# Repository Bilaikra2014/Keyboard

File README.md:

# ⌨️ WirelessKeyboard Project

Ce projet a pour objectif la conception et la fabrication d'un clavier mécanique (Filaire USB-C / Sans-fil). Le système repose sur un écosystème ESP32 permettant une communication rapide et personnalisée. Ce projet est une première version de test, une autre version pourrait être conçue dans le but de rechercher encore plus de perfomance en utilisant des composants plus adaptés.

## 📋 Présentation du projet

Le projet consiste à créer deux dispositifs distincts :
1.  **Le Clavier (Émetteur) :** Gère la matrice de touches, la batterie et la communication.
2.  **Le Récepteur (Dongle) :** Reçoit les données sans fil et les transmet à l'ordinateur via USB.

L'architecture se divise en trois axes de développement :
* **Électronique :** Conception des schémas et des PCB.
* **Informatique :** Développement des firmwares d'émission et de réception.
* **Mécanique :** Conception CAO 3D du boîtier du clavier et de celui dongle.

---

## 🛠️ Spécifications Matérielles

### 1. Le Clavier (ESP32-S3)
Le choix de l'**ESP32-S3** est motivé par son support **USB natif**, indispensable pour le mode filaire.
* **Prise USB C** pour le mode filaire.
* **Alimentation :** Batterie LiPo 1S (3.7V).
* **Régulation :** Passage du 5V(USB)/3v7(Batterie) vers 3.3V via un régulateur de tension (LDO).
* **Gestion de charge :** Circuit de charge intégré permettant :
    * L'alimentation du µC via USB lors du branchement.
    * La recharge simultanée de la batterie.
    * Le basculement automatique sur batterie lors du débranchement.

### 2. Le Récepteur (ESP32-S3-MINI)

L'**ESP32-S3-MINI** est utilisé pour son format compact et son coût réduit. Il fait office de pont entre le clavier et le PC.
* **Prise USB A** pour le brancher à l'ordinateur.
* **Interface :** Prise USB-A mâle.
* **Alimentation :** LDO convertissant le 5V USB en 3.3V.
* **Contrôles physiques :**
    * **Bouton BOOT :** Maintien du GPIO 9 à la masse pour le mode téléchargement.
    * **Bouton RESET :** Redémarrage du contrôleur pour les phases de test.
* **Câblage USB natif :**
    * `D+` ↔ GPIO 19
    * `D-` ↔ GPIO 18
    * `V+` ↔ Entrée LDO
    * `GND` ↔ Masse commune

---

## 📂 Structure du projet

Chaque sous-structure du projet aura son propre fichier Readme dédiée à la partie qu'elle traite.

```text
.
├── 📁 Electronique        # Schémas et PCB (KiCad)
│   ├── 📁 Lib              # Librairie Kicad
│   ├── 📁 Clavier          # Code de l'émetteur
│   └── 📁 Recepteur        # Code du récepteur
├── 📁 Informatique        # Code source ESP32
│   ├── 📁 Clavier          # Code de l'émetteur
│   └── 📁 Recepteur        # Code du récepteur
├── 📁 Mecanique          # Modèles 3D (STL/STEP)
└── README.md                #README global du projet

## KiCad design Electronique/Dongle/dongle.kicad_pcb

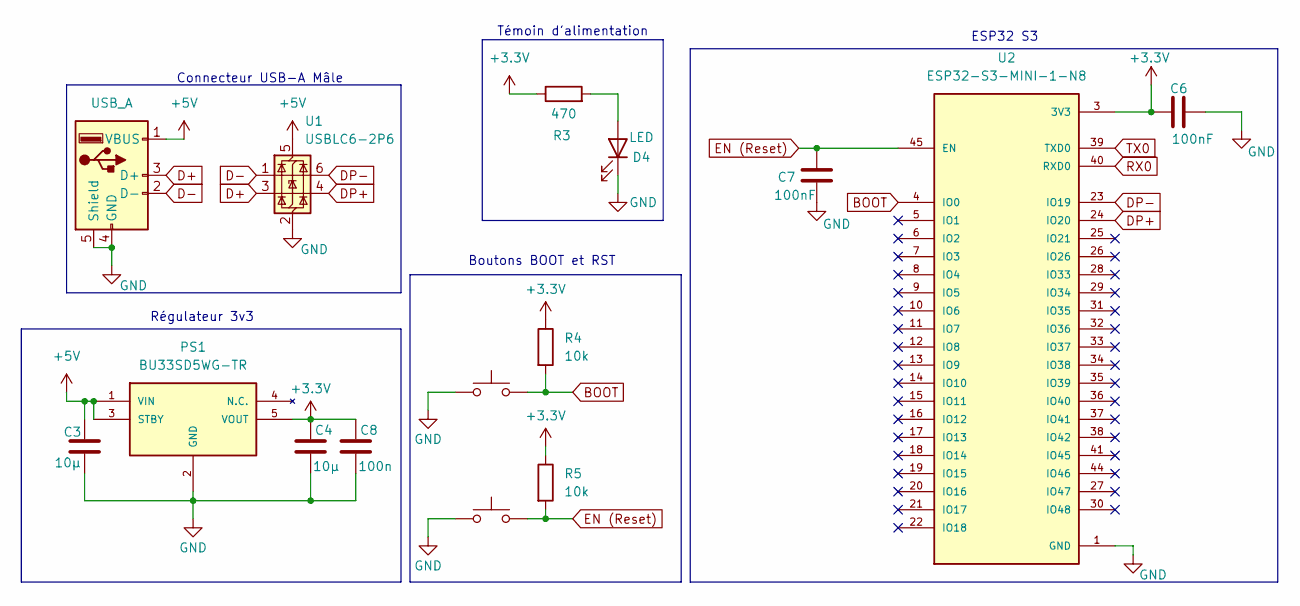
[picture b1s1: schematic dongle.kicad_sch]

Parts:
C3, C4: 10µ; C_0603_1608Metric_Pad1.08x0.95mm_HandSolder
C6, C7: 100nF; C_0603_1608Metric_Pad1.08x0.95mm_HandSolder
C8: 100n; C_0603_1608Metric_Pad1.08x0.95mm_HandSolder
D4: LED; LED_0603_1608Metric
J1: USB_A; USB_A_CNCTech_1001-011-01101_Horizontal
PS1: BU33SD5WG-TR; SOT95P280X125-5N; MOUSER_PART_NUMBER 755-BU33SD5WG-TR
R3: 470; R_0805_2012Metric
R4, R5: 10k; R_0805_2012Metric
SW3: BOOT; 434771025826
SW4: RST; 434771025826
U1: USBLC6-2P6; SOT-23-6
U2: ESP32-S3-MINI-1-N8; PARTREV v0.6

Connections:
+3.3V: C4.1, C6.2, C8.1, PS1.5 (VOUT), R3.1, R4.1, R5.1, U2.3 (3V3)
+5V: C3.1, J1.1 (VBUS), PS1.1 (VIN), PS1.3 (STBY), U1.5 (VBUS)
BOOT: R4.2, SW3.2, U2.4 (IO0)
D+: J1.3 (D+), U1.3 (I/O2)
D-: J1.2 (D-), U1.1 (I/O1)
DP+: U1.4 (I/O2), U2.24 (IO20)
DP-: U1.6 (I/O1), U2.23 (IO19)
EN (Reset): C7.1, R5.2, SW4.2, U2.45 (EN)
GND: C3.2, C4.2, C6.1, C7.2, C8.2, D4.1 (K), J1.4 (GND), J1.5 (Shield), PS1.2 (GND), SW3.1, SW4.1, U1.2 (GND), U2.1 (GND), U2.2 (GND), U2.42 (GND), U2.43 (GND), U2.46 (GND), U2.47 (GND), U2.48 (GND), U2.49 (GND), U2.50 (GND), U2.51 (GND), U2.52 (GND), U2.53 (GND), U2.54 (GND), U2.55 (GND), U2.56 (GND), U2.57 (GND), U2.58 (GND), U2.59 (GND), U2.60 (GND), U2.61 (GND), U2.61_1 (GND), U2.61_2 (GND), U2.61_3 (GND), U2.61_4 (GND), U2.61_5 (GND), U2.61_6 (GND), U2.61_7 (GND), U2.61_8 (GND), U2.62 (GND), U2.63 (GND), U2.64 (GND), U2.65 (GND)
unnamed: D4.2 (A), R3.2
RX0: U2.40 (RXD0)
TX0: U2.39 (TXD0)

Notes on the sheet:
Témoin d'alimentation
Connecteur USB-A Mâle
Boutons BOOT et RST
ESP32 S3
Régulateur 3v3

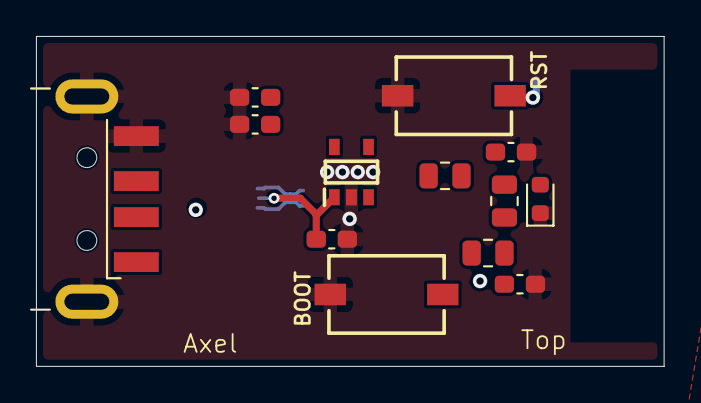
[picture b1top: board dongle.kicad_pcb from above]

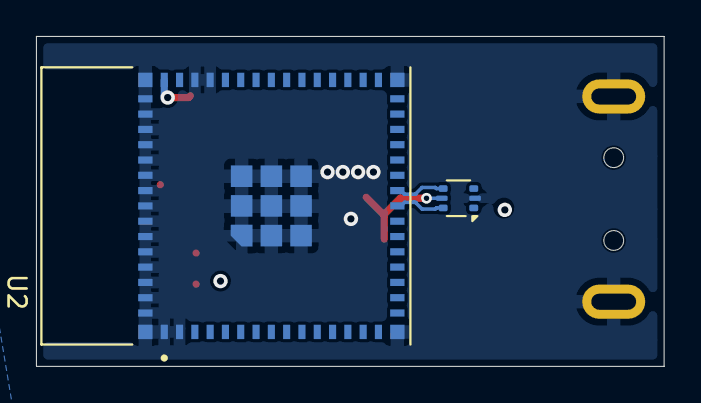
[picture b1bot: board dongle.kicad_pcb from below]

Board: 2 copper layers, 34.9 x 18.3 mm, 15 parts (2 on the bottom side), 10 nets.

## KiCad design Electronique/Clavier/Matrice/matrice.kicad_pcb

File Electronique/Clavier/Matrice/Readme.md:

# Partie electronique - Matrice de touche et encodeur
 
## Matrice de touche

Le clavier comporte 71 touches. Avec un système de surveillance normal des touches, il faudrait 71 GPIOs ce qui est beaucoup trop. Un système de matrice à donc été utilisé, permettant ainsi de réduire le nombre de broches utilisées. La matrice de touche se compose de 5 lignes et 15 colonnes, ce qui fait que l'on utiliser que 20 GPIOs. 

**Fonctionnement de la matrice** : 
- Le µC met successivement chaque ligne à l'état BAS.
- Il lit ensuite l'état des colonnes maintenues à l'état HAUT par des résistances de pull-up.
- Si une colonne est detectée à l'état BAS, c'est que la touche correspondant au croisement est activée.

**Le problème du Ghosting** : 

Sur une matrice simple, presser trois touches simultanément (ex: A, Q et S) peut créer un chemin de retour parasite. Le courant "remonte" par une ligne adjacente, faisant croire au contrôleur qu'une quatrième touche fantôme (Ghost) est pressée.
Pour pallier ce problème, chaque interrupteur est couplé à une diode de signal 1N4148 : 
- Rôle : Elle force le courant à circuler dans un seul sens (Ligne → Colonne).
- Résultat : Cela permet le N-Key Rollover (NKRO), garantissant que chaque pression de touche est enregistrée indépendamment, quel que soit le nombre de touches pressées simultanément.

Les touches utilisées sont des switchs mécanique **Cherry MX Red** commandés sur AliExpress.

## Gestion de l'encodeur

L'encodeur permet la gestion du volume.

L'encodeur utilisé (déjà présent à l'école) possède une fonction RGB avec les 3 diodes (pin 1,2 et 4) mais ne seront pas utilisée ici.

## Résultat final

Voici la vue 3D du Résultat final via logiciel :

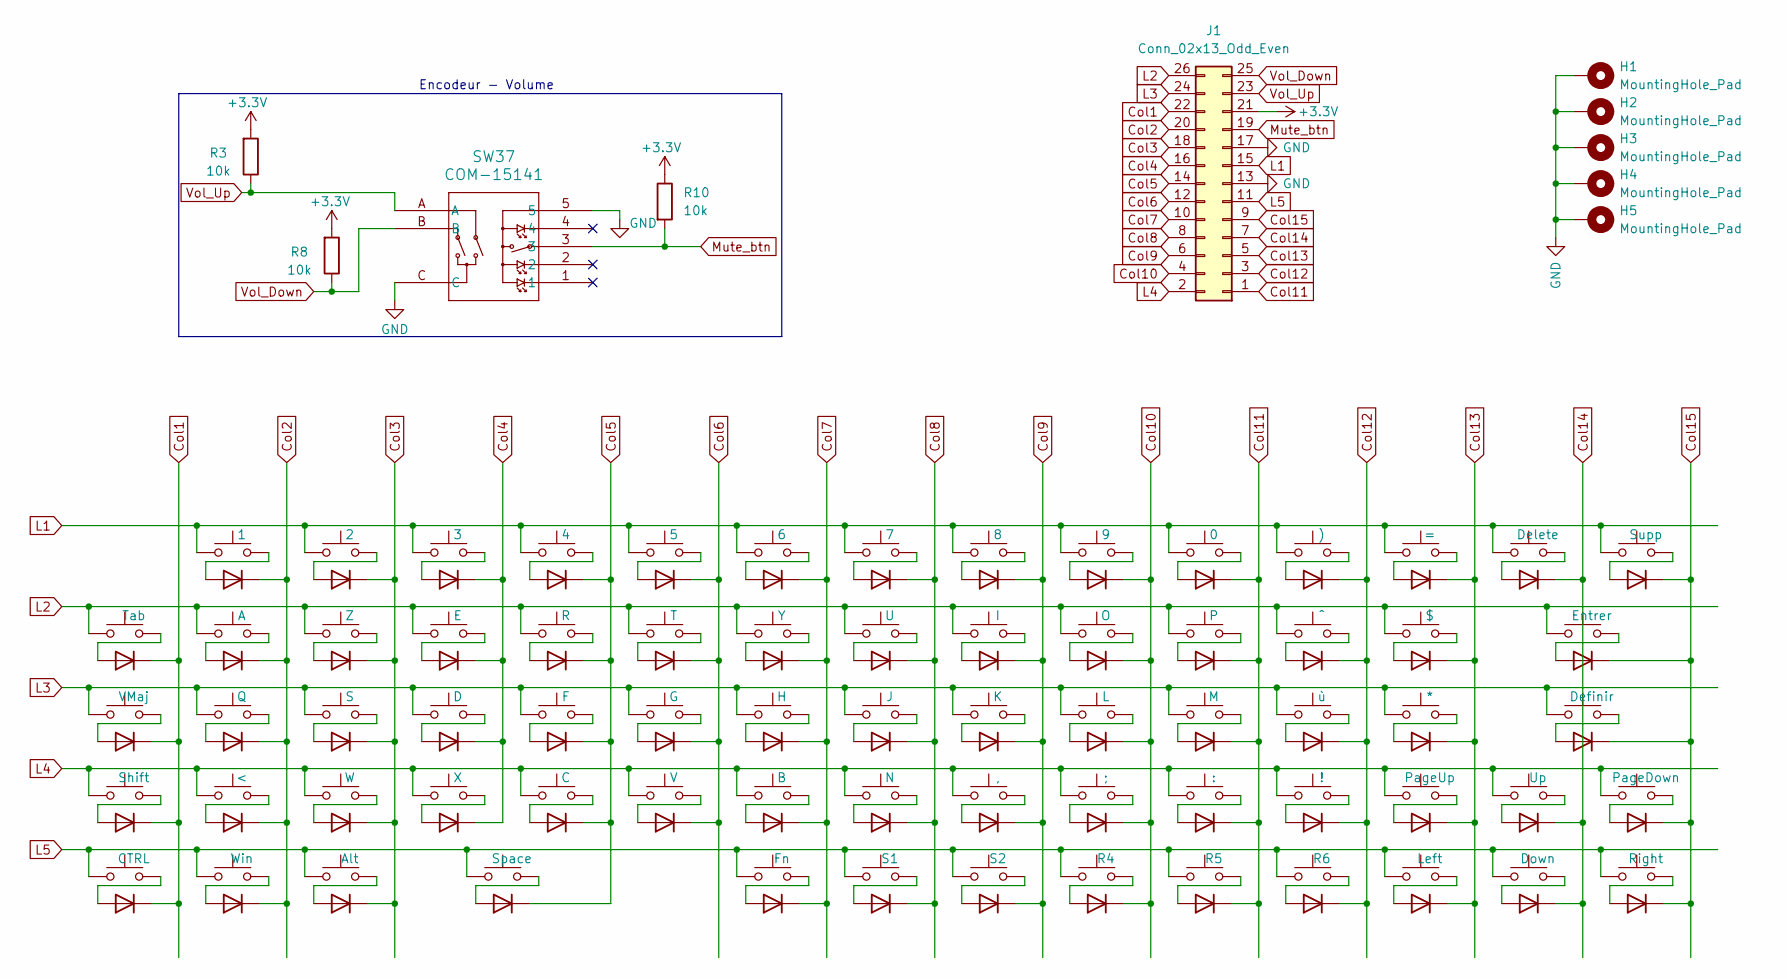
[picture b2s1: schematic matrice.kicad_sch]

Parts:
D2, D3, D4, D5, D6, D7, D8, D9, D10, D11, D12, D13, D14, D15, D16, D17, D18, D19, D20, D21, D22, D23, D24, D25, D26, D27, D28, D29, D30, D31, D32, D33, D34, D35, D36, D37, D38, D39, D40, D41, D42, D43, D44, D45, D46, D47, D48, D49, D50, D51, D52, D53, D54, D55, D56, D57, D58, D59, D60, D61, D62, D63, D64, D65, D66, D67, D69, D70, D71, D72: 1N4148WT; D_SOD-523
H1, H2, H3, H4, H5: MountingHole_Pad; MountingHole_3.2mm_M3_DIN965_Pad
J1: Conn_02x13_Odd_Even; IDC-Header_2x13_P2.54mm_Horizontal
R3, R8, R10: 10k; R_0805_2012Metric
SW2: Tab; SW_Cherry_MX_Plate_1.50u
SW3: VMaj; SW_Cherry_MX_Plate_2.00u
SW4: Shift; SW_Cherry_MX_Plate_1.25u
SW5: CTRL; SW_Cherry_MX_Plate_1.25u
SW6: 1; SW_Cherry_MX_Plate_1.00u
SW7: A; SW_Cherry_MX_Plate_1.00u
SW8: Q; SW_Cherry_MX_Plate_1.00u
SW9: <; SW_Cherry_MX_Plate_1.00u
SW10: Win; SW_Cherry_MX_Plate_1.25u
SW11: 2; SW_Cherry_MX_Plate_1.00u
SW12: Z; SW_Cherry_MX_Plate_1.00u
SW13: S; SW_Cherry_MX_Plate_1.00u
SW14: W; SW_Cherry_MX_Plate_1.00u
SW15: Alt; SW_Cherry_MX_Plate_1.25u
SW16: 3; SW_Cherry_MX_Plate_1.00u
SW17: E; SW_Cherry_MX_Plate_1.00u
SW18: D; SW_Cherry_MX_Plate_1.00u
SW19: X; SW_Cherry_MX_Plate_1.00u
SW20: 4; SW_Cherry_MX_Plate_1.00u
SW21: R; SW_Cherry_MX_Plate_1.00u
SW22: F; SW_Cherry_MX_Plate_1.00u
SW23: C; SW_Cherry_MX_Plate_1.00u
SW24: 5; SW_Cherry_MX_Plate_1.00u
SW25: T; SW_Cherry_MX_Plate_1.00u
SW26: G; SW_Cherry_MX_Plate_1.00u
SW27: V; SW_Cherry_MX_Plate_1.00u
SW28: Space; SW_Cherry_MX_Plate_1.75u
SW29: 6; SW_Cherry_MX_Plate_1.00u
SW30: Y; SW_Cherry_MX_Plate_1.00u
SW31: H; SW_Cherry_MX_Plate_1.00u
SW32: B; SW_Cherry_MX_Plate_1.00u
SW33: 7; SW_Cherry_MX_Plate_1.00u
SW34: U; SW_Cherry_MX_Plate_1.00u
SW35: J; SW_Cherry_MX_Plate_1.00u
SW36: N; SW_Cherry_MX_Plate_1.00u
SW37: COM-15141; COM-15141_SPK
SW38: 8; SW_Cherry_MX_Plate_1.00u
SW39: I; SW_Cherry_MX_Plate_1.00u
SW40: K; SW_Cherry_MX_Plate_1.00u
SW41: ,; SW_Cherry_MX_Plate_1.00u
SW42: 9; SW_Cherry_MX_Plate_1.00u
SW43: O; SW_Cherry_MX_Plate_1.00u
SW44: L; SW_Cherry_MX_Plate_1.00u
SW45: ;; SW_Cherry_MX_Plate_1.00u
SW46: 0; SW_Cherry_MX_Plate_1.00u
SW47: P; SW_Cherry_MX_Plate_1.00u
SW48: M; SW_Cherry_MX_Plate_1.00u
SW49: :; SW_Cherry_MX_Plate_1.00u
SW50: R5; SW_Cherry_MX_Plate_1.00u
SW51: ); SW_Cherry_MX_Plate_1.00u
SW52: ^; SW_Cherry_MX_Plate_1.00u
SW53: ù; SW_Cherry_MX_Plate_1.00u
SW54: !; SW_Cherry_MX_Plate_1.00u
SW55: R6; SW_Cherry_MX_Plate_1.00u
SW56: =; SW_Cherry_MX_Plate_1.00u
SW57: $; SW_Cherry_MX_Plate_1.00u
SW58: *; SW_Cherry_MX_Plate_1.00u
SW59: PageUp; SW_Cherry_MX_Plate_1.00u
SW60: Left; SW_Cherry_MX_Plate_1.00u
SW61: Delete; SW_Cherry_MX_Plate_1.00u
SW62: Up; SW_Cherry_MX_Plate_1.00u
SW63: Down; SW_Cherry_MX_Plate_1.00u
SW64: Entrer; SW_Cherry_MX_Plate_1.75u
SW65: Definir; SW_Cherry_MX_Plate_1.25u
SW66: Supp; SW_Cherry_MX_Plate_1.25u
SW67: PageDown; SW_Cherry_MX_Plate_1.00u
SW68: Right; SW_Cherry_MX_Plate_1.00u
SW70: Fn; SW_Cherry_MX_Plate_1.25u
SW71: S1; SW_Cherry_MX_Plate_1.25u
SW72: S2; SW_Cherry_MX_Plate_1.25u
SW73: R4; SW_Cherry_MX_Plate_1.00u

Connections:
+3.3V: J1.21, R3.2, R8.2, R10.1
Col1: D2.1 (K), D3.1 (K), D4.1 (K), D5.1 (K), J1.22
Col2: D6.1 (K), D7.1 (K), D8.1 (K), D9.1 (K), D10.1 (K), J1.20
Col3: D11.1 (K), D12.1 (K), D13.1 (K), D14.1 (K), D15.1 (K), J1.18
Col4: D16.1 (K), D17.1 (K), D18.1 (K), D19.1 (K), J1.16
Col5: D20.1 (K), D21.1 (K), D22.1 (K), D23.1 (K), D28.1 (K), J1.14
Col6: D24.1 (K), D25.1 (K), D26.1 (K), D27.1 (K), J1.12
Col7: D29.1 (K), D30.1 (K), D31.1 (K), D32.1 (K), D69.1 (K), J1.10
Col8: D33.1 (K), D34.1 (K), D35.1 (K), D36.1 (K), D70.1 (K), J1.8
Col9: D37.1 (K), D38.1 (K), D39.1 (K), D40.1 (K), D71.1 (K), J1.6
Col10: D41.1 (K), D42.1 (K), D43.1 (K), D44.1 (K), D72.1 (K), J1.4
Col11: D45.1 (K), D46.1 (K), D47.1 (K), D48.1 (K), D49.1 (K), J1.1
Col12: D50.1 (K), D51.1 (K), D52.1 (K), D53.1 (K), D54.1 (K), J1.3
Col13: D55.1 (K), D56.1 (K), D57.1 (K), D58.1 (K), D59.1 (K), J1.5
Col14: D60.1 (K), D61.1 (K), D62.1 (K), J1.7
Col15: D63.1 (K), D64.1 (K), D65.1 (K), D66.1 (K), D67.1 (K), J1.9
GND: H1.1 (1_1), H2.1 (1_1), H3.1 (1_1), H4.1 (1_1), H5.1 (1_1), J1.13, J1.17, SW37.5, SW37.C
L1: J1.15, SW6.1, SW11.1, SW16.1, SW20.1, SW24.1, SW29.1, SW33.1, SW38.1, SW42.1, SW46.1, SW51.1, SW56.1, SW61.1, SW66.1
L2: J1.26, SW2.1, SW7.1, SW12.1, SW17.1, SW21.1, SW25.1, SW30.1, SW34.1, SW39.1, SW43.1, SW47.1, SW52.1, SW57.1, SW64.1
L3: J1.24, SW3.1, SW8.1, SW13.1, SW18.1, SW22.1, SW26.1, SW31.1, SW35.1, SW40.1, SW44.1, SW48.1, SW53.1, SW58.1, SW65.1
L4: J1.2, SW4.1, SW9.1, SW14.1, SW19.1, SW23.1, SW27.1, SW32.1, SW36.1, SW41.1, SW45.1, SW49.1, SW54.1, SW59.1, SW62.1, SW67.1
L5: J1.11, SW5.1, SW10.1, SW15.1, SW28.1, SW50.1, SW55.1, SW60.1, SW63.1, SW68.1, SW70.1, SW71.1, SW72.1, SW73.1
Mute_btn: J1.19, R10.2, SW37.3
unnamed: D2.2 (A), SW2.2
unnamed: D3.2 (A), SW3.2
unnamed: D4.2 (A), SW4.2
unnamed: D5.2 (A), SW5.2
unnamed: D6.2 (A), SW6.2
unnamed: D7.2 (A), SW7.2
unnamed: D8.2 (A), SW8.2
unnamed: D9.2 (A), SW9.2
unnamed: D10.2 (A), SW10.2
unnamed: D11.2 (A), SW11.2
unnamed: D12.2 (A), SW12.2
unnamed: D13.2 (A), SW13.2
unnamed: D14.2 (A), SW14.2
unnamed: D15.2 (A), SW15.2
unnamed: D16.2 (A), SW16.2
unnamed: D17.2 (A), SW17.2
unnamed: D18.2 (A), SW18.2
unnamed: D19.2 (A), SW19.2
unnamed: D20.2 (A), SW20.2
unnamed: D21.2 (A), SW21.2
unnamed: D22.2 (A), SW22.2
unnamed: D23.2 (A), SW23.2
unnamed: D24.2 (A), SW24.2
unnamed: D25.2 (A), SW25.2
unnamed: D26.2 (A), SW26.2
unnamed: D27.2 (A), SW27.2
unnamed: D28.2 (A), SW28.2
unnamed: D29.2 (A), SW29.2
unnamed: D30.2 (A), SW30.2
unnamed: D31.2 (A), SW31.2
unnamed: D32.2 (A), SW32.2
unnamed: D33.2 (A), SW33.2
unnamed: D34.2 (A), SW34.2
unnamed: D35.2 (A), SW35.2
unnamed: D36.2 (A), SW36.2
unnamed: D37.2 (A), SW38.2
unnamed: D38.2 (A), SW39.2
unnamed: D39.2 (A), SW40.2
unnamed: D40.2 (A), SW41.2
unnamed: D41.2 (A), SW42.2
unnamed: D42.2 (A), SW43.2
unnamed: D43.2 (A), SW44.2
unnamed: D44.2 (A), SW45.2
unnamed: D45.2 (A), SW46.2
unnamed: D46.2 (A), SW47.2
unnamed: D47.2 (A), SW48.2
unnamed: D48.2 (A), SW49.2
unnamed: D49.2 (A), SW50.2
unnamed: D50.2 (A), SW51.2
unnamed: D51.2 (A), SW52.2
unnamed: D52.2 (A), SW53.2
unnamed: D53.2 (A), SW54.2
unnamed: D54.2 (A), SW55.2
unnamed: D55.2 (A), SW56.2
unnamed: D56.2 (A), SW57.2
unnamed: D57.2 (A), SW58.2
unnamed: D58.2 (A), SW59.2
unnamed: D59.2 (A), SW60.2
unnamed: D60.2 (A), SW61.2
unnamed: D61.2 (A), SW62.2
unnamed: D62.2 (A), SW63.2
unnamed: D63.2 (A), SW64.2
unnamed: D64.2 (A), SW65.2
unnamed: D65.2 (A), SW66.2
unnamed: D66.2 (A), SW67.2
unnamed: D67.2 (A), SW68.2
unnamed: D69.2 (A), SW70.2
unnamed: D70.2 (A), SW71.2
unnamed: D71.2 (A), SW72.2
unnamed: D72.2 (A), SW73.2
Vol_Down: J1.25, R8.1, SW37.B
Vol_Up: J1.23, R3.1, SW37.A

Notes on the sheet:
Encodeur - Volume

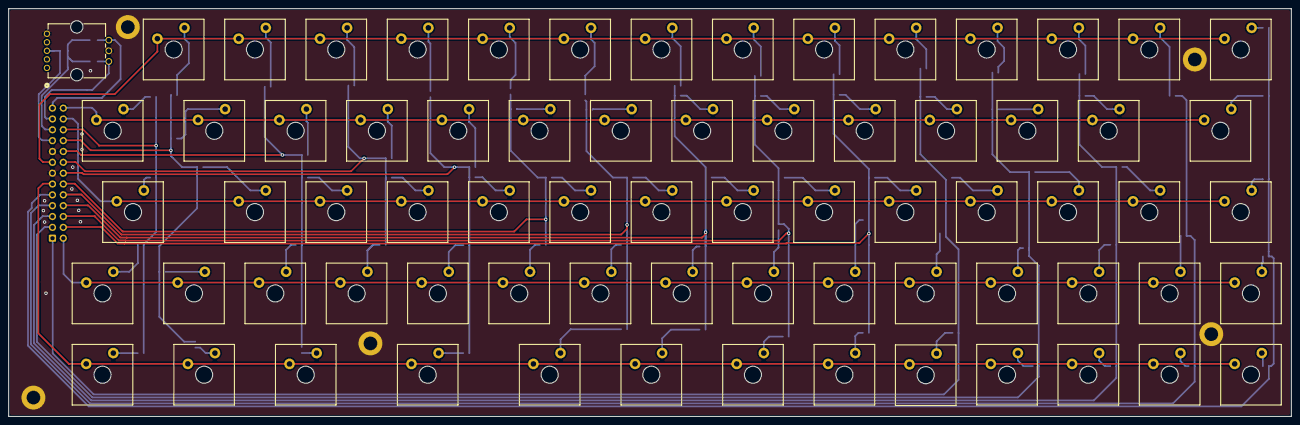
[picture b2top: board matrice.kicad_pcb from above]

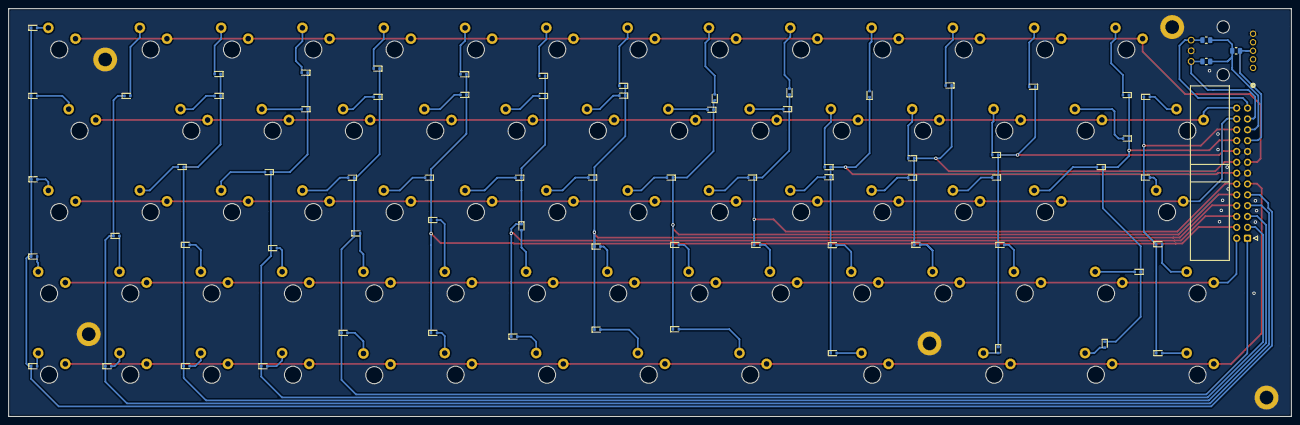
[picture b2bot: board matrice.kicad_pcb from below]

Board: 2 copper layers, 300.5 x 95.5 mm, 150 parts (74 on the bottom side), 95 nets.

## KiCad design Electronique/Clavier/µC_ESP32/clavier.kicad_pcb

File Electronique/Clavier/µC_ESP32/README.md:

# Partie electronique - Microcontrôleur
## Gestion d'alimentation et Chargeur Li-Po

Lorsque la batterie est déchargée, le clavier sera branché à l'ordinateur via une prise USB. La prise de l'ordinateur va alimenter le clavier, et charger la batterie avec le courant restant. Une prise USB A d'ordinateur peut fournir en général jusqu'à 500 mA. 

Pour gérer l'alimentation et la charge, le composant utilisé sera le [MCP73871](https://ww1.microchip.com/downloads/en/DeviceDoc/MCP73871-Data-Sheet-20002090E.pdf) qui permet : 
  - **Gestion du Power Path** : Alimente le système depuis l'USB tout en gérant la charge la batterie
  - **Partage du courant** : Donne la priorité à l'alimentation du système, le courant restant est alloué à la charge de la batterie

<div align="center">
</div>

**Alimentation et Puissance**
  - In (18) : Alimentation du composant -> USB
  - Out (20) : Alimentation du système -> Régulateur LDO
  - Vbat (14) : Charge de la batterie -> Vbat
  - Vss (10) : Masse -> GND

**Contrôle et Logique**:
  - SEL (3) : Limite de courant à tirer sur l'USB -> LOW pour 500 mA (HIGH pour 1,8)
  - PROG2 (4) : Courant d'entré max à tirer -> HIGH pour 500 mA (HIGH pour 100mA)  
  - CE (17) : Activation du système à l'état haut -> Vusb
  - TE (9) : Sécurité interne du temps de charge -> GND

**Programmation et Sécurité**:
  - PROG1 (13) : Courant de charge rapide -> R = 1000V/Ireg, on veut Ireg = 250mA donc R = 4k
  - PROG3 (12) : Seuil de fin de charge -> R = 40k
  - VPCC (2)   : 
  - VBAT_S (16): Sonde de tension -> Vbat
  - THERM (5)  : Capteur de temperature ->  

**Indicateurs visuel**: Ces broches tirent vers la masse, on y connecte des leds
  - PG (6)    : Indication que l'USB est branché, à brancher à l'ESP32 pour qu'il detecte si on est sur batterie ou USB
  - STAT1 (8) : Indication de la phase de charge 
  - STAT2 (7) : Indication de la fin de charge 

## Régulateur de tension

Le µC sera alimenté par du 5v ou bien du 3v7, or il n'accepte que du 3v3. Il faut donc utiliser un régulateur de tension. Le régulateur de tension utilisé est un [BU33SD5WGTR](https://www.rohm.com/products/power-management/linear-regulators/single-output-ldo-regulators/bu33sd5wg-product).

## Mesure de la batterie

La mesure de la batterie permet d'indiquer à l'utilisateur si le clavier à besoin d'être chargé ou pas. La tension étant supérieur aux 3v3 de l'esp32, il faut diviser cette tension pour qu'elle puisse être lue par l'esp32 à travers un pont diviseur de tension.

**Pont Diviseur de tension**:

Le pont diviseur de tension formé par R16 et R17 permet d'ajuster la tension mesurée par L'ESP32. La tension de la batterie varie entre 4v2 et 3v7, ce qui donnera pour l'ESP32 une tension mesurée entre 3v et 2,64v, ce qui est dans la plage de donnée mesurable.

**Ajout des transistors Q3 et Q4**:

Utiliser simplement un pont diviseur consommerait du courant en permanance, aussi minime soit-il. C'est pour cela que des transistors ont été ajouté. Le transistor Q2 est un mosfet canal P, qui lie la batterie au pont diviseur lorsqu'il est passant. Ce transistor est piloté par son complémentaire Q1, un canal N commandé par l'esp32. Ce transistor sera passant uniquement lors de la mesure déclenchée par l'ESP32. La résistance R15 sert de pull-up pour maintenir le transistor Q2 bloqué quand Q1 est bloqué. Ce montage permet de relier le pont diviseur à la batterie uniquement lors de la mesure, limitant ainsi la consommation du pont diviseur.

## USB-C et protection ESD

Le port USB-C permet l'utilisation filaire du clavier, ainsi que la recharge de la batterie.

Les broches D+ et D- permettent la communication ESP32-Ordinateur. 
Les broches CC1 et CC2 doivent être liées à des résistances de 5k1 de pull-down pour que la source détecte la présence du clavier et délivre ainsi le 5v.

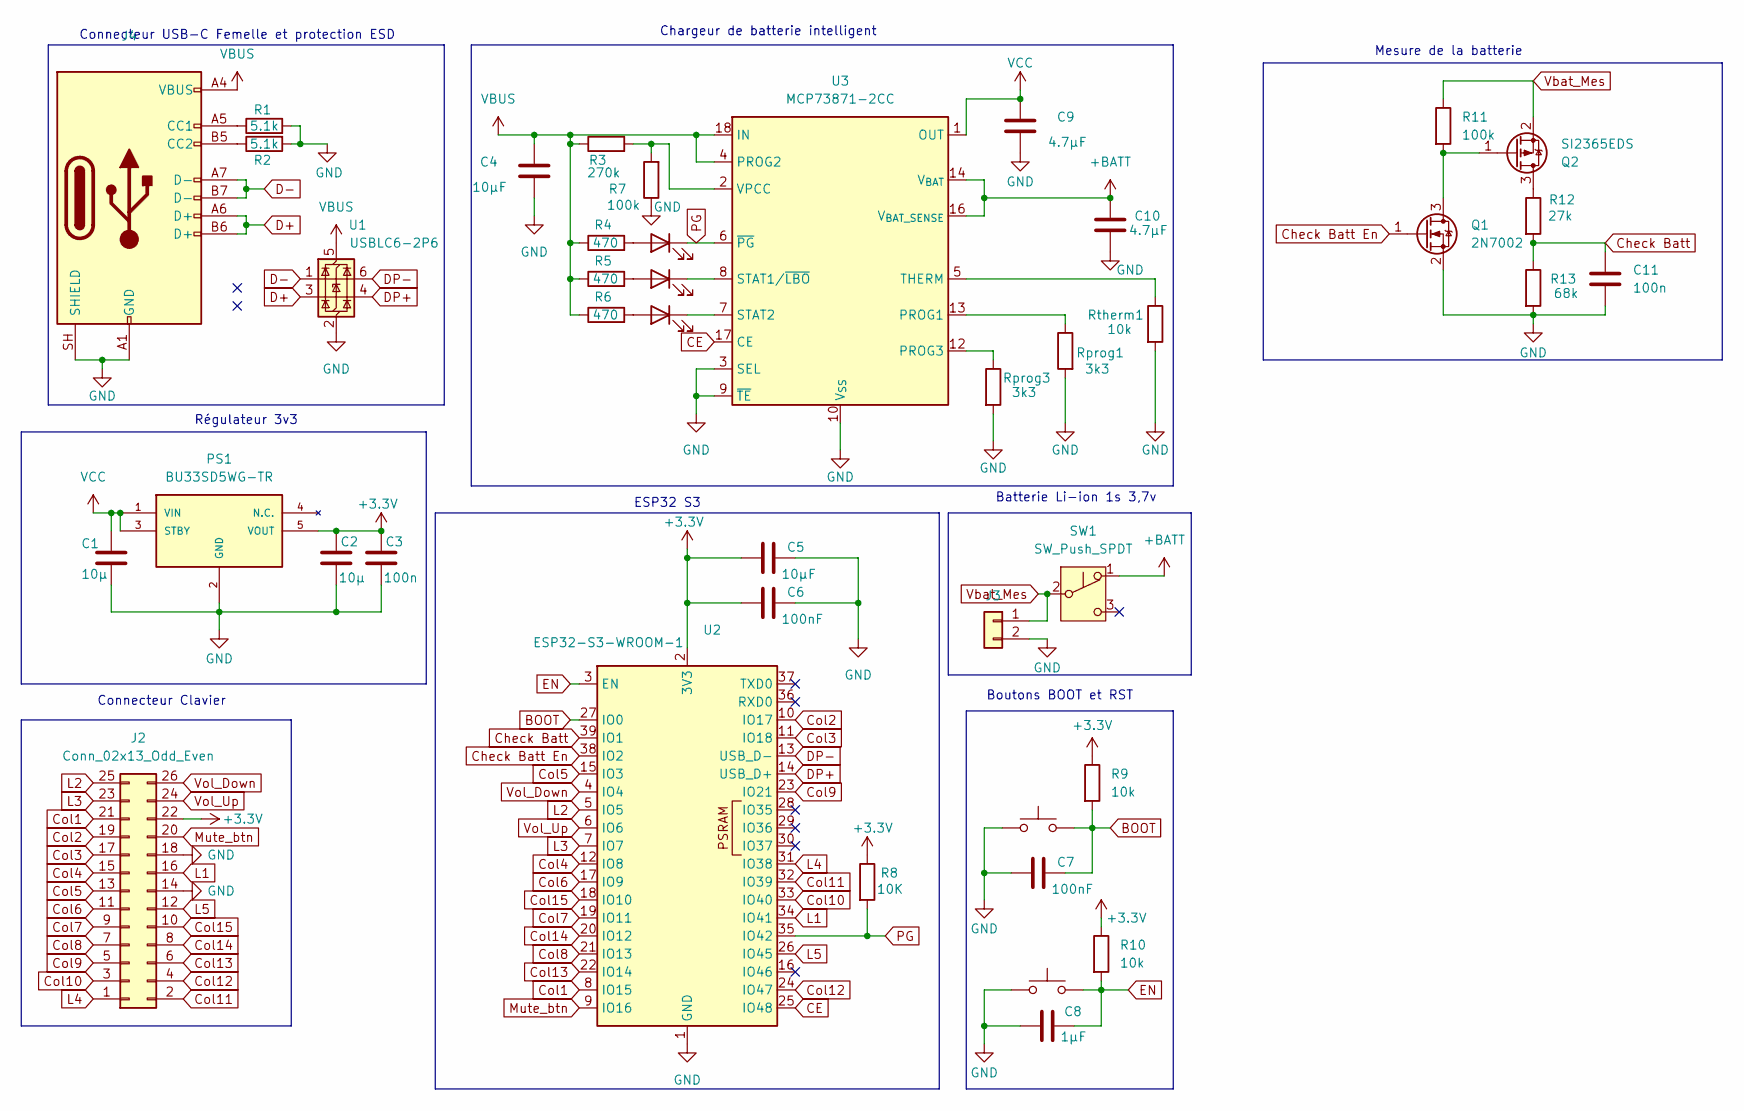
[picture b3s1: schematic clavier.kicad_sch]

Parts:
BOOT1: SW_Push; 434771025826
C1, C2: 10µ; C_0603_1608Metric_Pad1.08x0.95mm_HandSolder
C3, C11: 100n; C_0603_1608Metric_Pad1.08x0.95mm_HandSolder
C4, C5: 10µF; C_0603_1608Metric_Pad1.08x0.95mm_HandSolder
C6, C7: 100nF; C_0603_1608Metric_Pad1.08x0.95mm_HandSolder
C8: 1µF; C_0603_1608Metric_Pad1.08x0.95mm_HandSolder
C9, C10: 4.7µF; C_0603_1608Metric_Pad1.08x0.95mm_HandSolder
J2: Conn_02x13_Odd_Even; PinHeader_2x13_P2.54mm_Vertical
J3: JST_PH_S2B-PH-K_1x02_P2.00mm_Horizontal
J4: USB_C_Receptacle_USB2.0_14P; USB_C_Receptacle_XKB_U262-16XN-4BVC11
PG1: LED; LED_0603_1608Metric
PS1: BU33SD5WG-TR; SOT95P280X125-5N; MOUSER_PART_NUMBER 755-BU33SD5WG-TR
Q1: 2N7002; SOT-23
Q2: SI2365EDS; SOT-23
R1, R2: 5.1k; R_0805_2012Metric
R3: 270k; R_0805_2012Metric
R4, R5, R6: 470; R_0805_2012Metric
R7, R11: 100k; R_0805_2012Metric
R8: 10K; R_0805_2012Metric
R9, R10: 10k; R_0805_2012Metric
R12: 27k; R_0805_2012Metric
R13: 68k; R_0805_2012Metric
RST1: SW_Push; 434771025826
Rprog1, Rprog3: 3k3; R_0805_2012Metric
Rtherm1: 10k; R_0805_2012Metric
STAT1, STAT2: LED; LED_0603_1608Metric
SW1: SW_Push_SPDT; SW_Slide-03_Wuerth-WS-SLTV_10x2.5x6.4_P2.54mm
U1: USBLC6-2P6; SOT-23-6
U2: ESP32-S3-WROOM-1
U3: MCP73871-2CC; QFN-20-1EP_4x4mm_P0.5mm_EP2.5x2.5mm

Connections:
+3.3V: C2.1, C3.1, C5.2, C6.2, J2.22, PS1.5 (VOUT), R8.1, R9.1, R10.1, U2.2 (3V3)
+BATT: C10.1, SW1.1 (A), U3.14 (V_{BAT}), U3.15 (V_{BAT}), U3.16 (V_{BAT_SENSE})
BOOT: BOOT1.2, C7.1, R9.2, U2.27 (IO0)
CE: U2.25 (IO48), U3.17 (CE)
Check Batt: C11.2, R12.2, R13.1, U2.39 (IO1)
Check Batt En: Q1.1 (G), U2.38 (IO2)
Col1: J2.21, U2.8 (IO15)
Col2: J2.19, U2.10 (IO17)
Col3: J2.17, U2.11 (IO18)
Col4: J2.15, U2.12 (IO8)
Col5: J2.13, U2.15 (IO3)
Col6: J2.11, U2.17 (IO9)
Col7: J2.9, U2.19 (IO11)
Col8: J2.7, U2.21 (IO13)
Col9: J2.5, U2.23 (IO21)
Col10: J2.3, U2.33 (IO40)
Col11: J2.2, U2.32 (IO39)
Col12: J2.4, U2.24 (IO47)
Col13: J2.6, U2.22 (IO14)
Col14: J2.8, U2.20 (IO12)
Col15: J2.10, U2.18 (IO10)
D+: J4.A6 (D+), J4.B6 (D+), U1.3 (I/O2)
D-: J4.A7 (D-), J4.B7 (D-), U1.1 (I/O1)
DP+: U1.4 (I/O2), U2.14 (USB_D+)
DP-: U1.6 (I/O1), U2.13 (USB_D-)
EN: C8.1, R10.2, RST1.2, U2.3 (EN)
GND: BOOT1.1, C1.2, C2.2, C3.2, C4.2, C5.1, C6.1, C7.2, C8.2, C9.2, C10.2, C11.1, J2.14, J2.18, J3.2, J4.A1 (GND), J4.A12 (GND), J4.B1 (GND), J4.B12 (GND), J4.SH (SHIELD), PS1.2 (GND), Q1.2 (S), R1.2, R2.2, R7.1, R13.2, RST1.1, Rprog1.2, Rprog3.2, Rtherm1.2, U1.2 (GND), U2.1 (GND), U2.40 (GND), U2.41 (GND), U3.3 (SEL), U3.9 (~TE), U3.10 (V_{SS}), U3.11 (V_{SS}), U3.21 (V_{SS})
L1: J2.16, U2.34 (IO41)
L2: J2.25, U2.5 (IO5)
L3: J2.23, U2.7 (IO7)
L4: J2.1, U2.31 (IO38)
L5: J2.12, U2.26 (IO45)
Mute_btn: J2.20, U2.9 (IO16)
unnamed: J4.A5 (CC1), R1.1
unnamed: J4.B5 (CC2), R2.1
unnamed: PG1.2 (A), R4.2
unnamed: Q1.3 (D), Q2.1 (G), R11.2
unnamed: Q2.3 (D), R12.1
unnamed: R5.2, STAT1.2 (A)
unnamed: STAT1.1 (K), U3.8 (STAT1/~LBO)
unnamed: R6.2, STAT2.2 (A)
unnamed: STAT2.1 (K), U3.7 (STAT2)
unnamed: Rprog1.1, U3.13 (PROG1)
unnamed: Rprog3.1, U3.12 (PROG3)
unnamed: Rtherm1.1, U3.5 (THERM)
unnamed: R3.2, R7.2, U3.2 (VPCC)
PG: PG1.1 (K), R8.2, U2.35 (IO42), U3.6 (~PG)
VBUS: C4.1, J4.A4 (VBUS), J4.A9 (VBUS), J4.B4 (VBUS), J4.B9 (VBUS), R3.1, R4.1, R5.1, R6.1, U1.5 (VBUS), U3.4 (PROG2), U3.18 (IN), U3.19 (IN)
VCC: C1.1, C9.1, PS1.1 (VIN), PS1.3 (STBY), U3.1 (OUT), U3.20 (OUT)
Vbat_Mes: J3.1, Q2.2 (S), R11.1, SW1.2 (B)
Vol_Down: J2.26, U2.4 (IO4)
Vol_Up: J2.24, U2.6 (IO6)

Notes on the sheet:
Chargeur de batterie intelligent
Mesure de la batterie
Boutons BOOT et RST
Connecteur Clavier
Batterie Li-ion 1s 3,7v
ESP32 S3
Connecteur USB-C Femelle et protection ESD
Régulateur 3v3

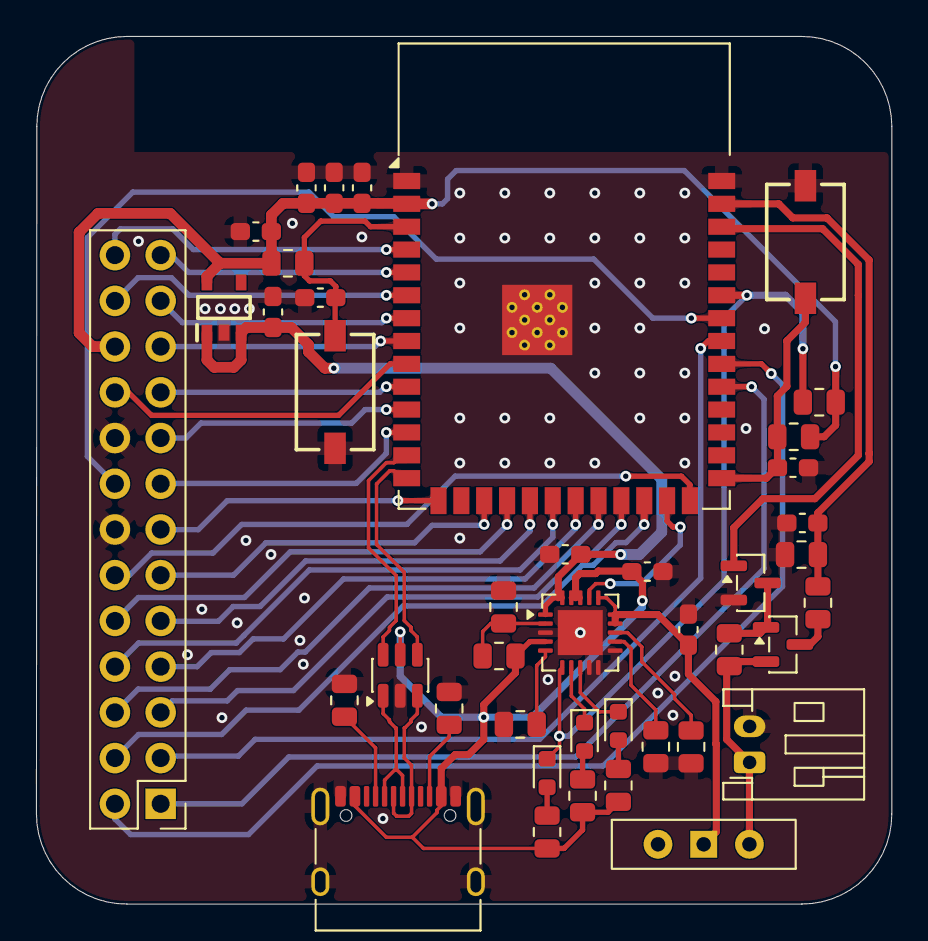
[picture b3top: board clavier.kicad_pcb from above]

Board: 2 copper layers, 47.5 x 48.2 mm, 42 parts (0 on the bottom side), 52 nets.

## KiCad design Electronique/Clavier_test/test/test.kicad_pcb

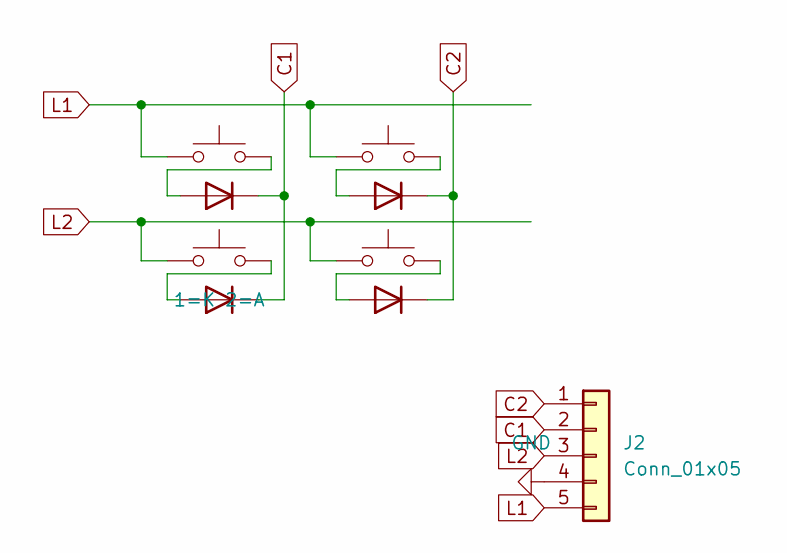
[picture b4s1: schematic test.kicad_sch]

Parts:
D1, D2, D3, D4: 1N4148; D_0603_1608Metric
J2: Conn_01x05; PinHeader_1x05_P2.54mm_Vertical
SW1, SW2, SW3, SW4: SW_Push; SW_Cherry_MX_1.00u_PCB

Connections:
C1: D1.1 (K), D2.1 (K), J2.2
C2: D3.1 (K), D4.1 (K), J2.1
GND: J2.4
L1: J2.5, SW1.1, SW3.1
L2: J2.3, SW2.1, SW4.1
unnamed: D1.2 (A), SW1.2
unnamed: D2.2 (A), SW2.2
unnamed: D3.2 (A), SW3.2
unnamed: D4.2 (A), SW4.2

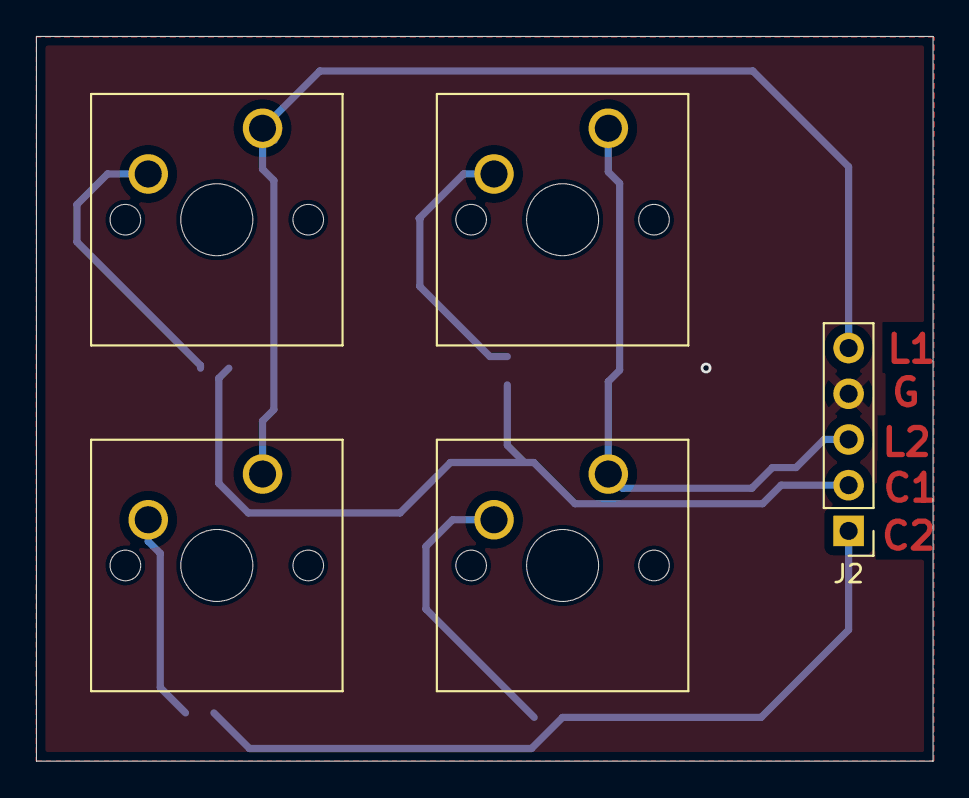
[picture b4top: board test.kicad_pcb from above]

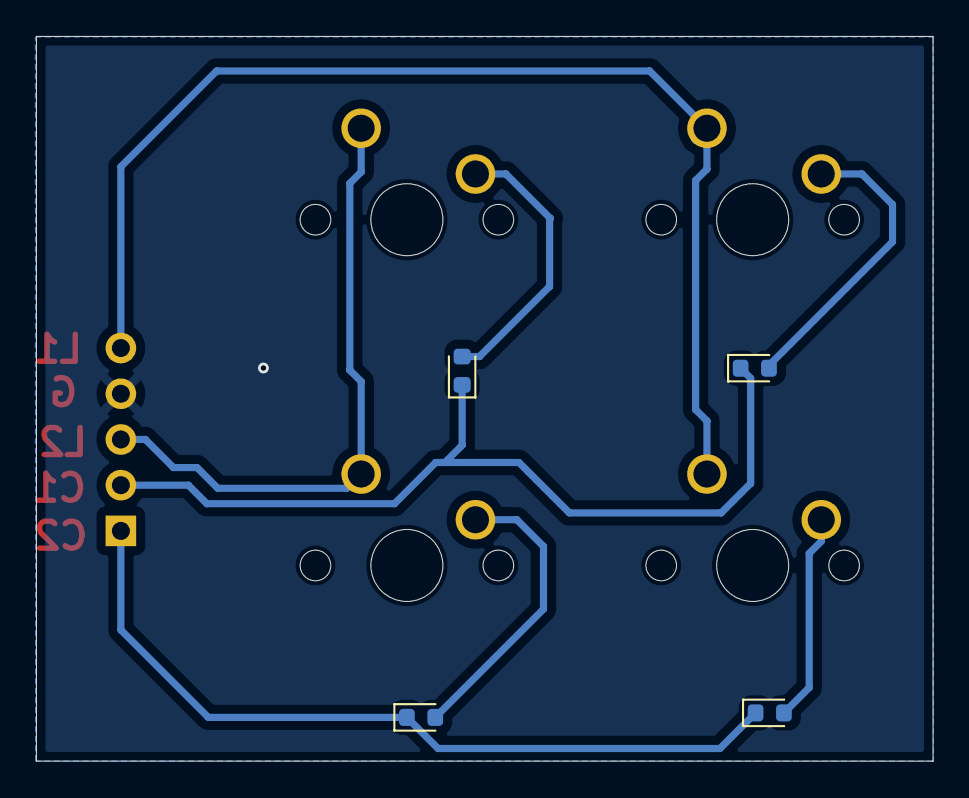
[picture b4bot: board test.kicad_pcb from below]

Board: 2 copper layers, 49.8 x 40.3 mm, 9 parts (4 on the bottom side), 8 nets.
